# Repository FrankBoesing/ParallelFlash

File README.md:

# ParallelFlash

Compatibel to SerialFlash by Paul Stoffregen

Winbond SPI Flash only.

Connections:

Pin 1 (Flash) : Pin 5 (Teensy)

Pin 2 (Flash) : Pin 14(Teensy)

Pin 3 (Flash) : Pin 7(Teensy)

Pin 4 (Flash) : GND

Pin 5 (Flash) : Pin 2(Teensy)

Pin 6 (Flash) : Pin 20(Teensy)

Pin 7 (Flash) : Pin 8(Teensy)

Pin 8 (Flash) : 3.3Volt

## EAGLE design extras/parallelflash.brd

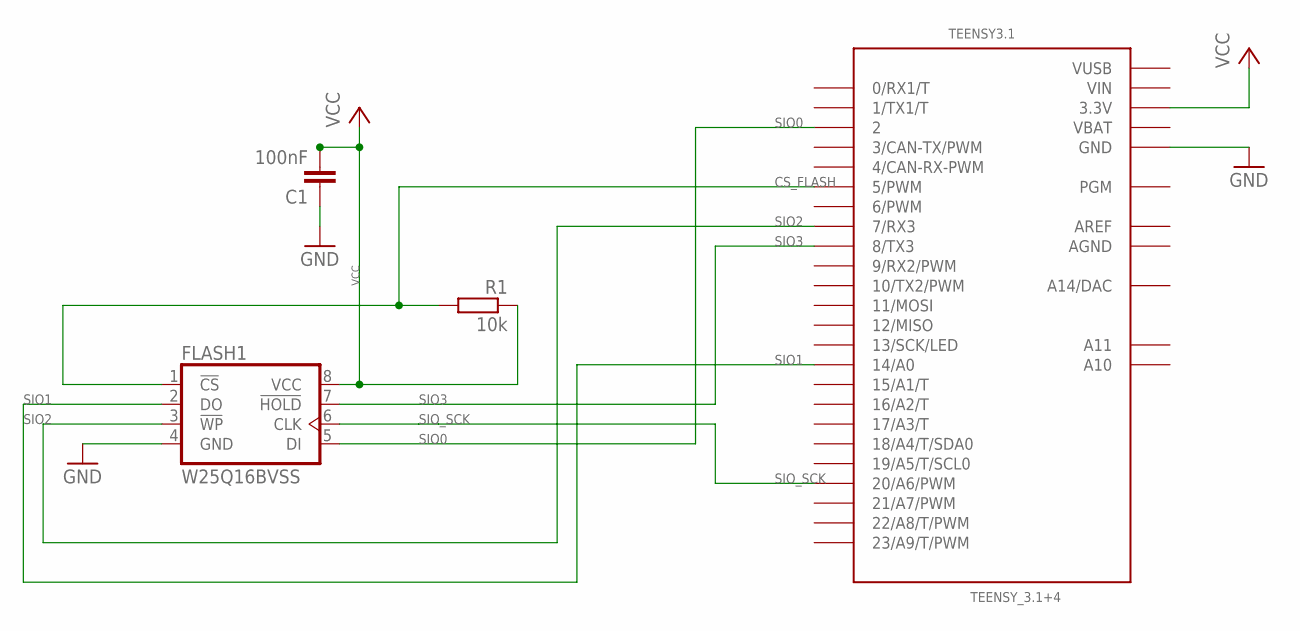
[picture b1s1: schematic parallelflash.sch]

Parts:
C1: 100nF; C0603
FLASH1: W25Q16BVSS; SO08-SS
R1: 10k; R0603
TEENSY3.1: TEENSY_3.1+4

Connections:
AGND: TEENSY3.1.AGND
AREF: TEENSY3.1.AREF
CS_FLASH: FLASH1.1 (!CS!), R1.2, TEENSY3.1.5 (5/PWM)
GND: C1.1, FLASH1.4 (GND), TEENSY3.1.GND, TEENSY3.1.GND1 (GND)
SIO0: FLASH1.5 (DI), TEENSY3.1.2
SIO1: FLASH1.2 (DO), TEENSY3.1.14/A0
SIO2: FLASH1.3 (!WP!), TEENSY3.1.7 (7/RX3)
SIO3: FLASH1.7 (!HOLD!), TEENSY3.1.8 (8/TX3)
SIO_SCK: FLASH1.6 (CLK), TEENSY3.1.20/A6 (20/A6/PWM)
VBAT: TEENSY3.1.VBAT
VCC: C1.2, FLASH1.8 (VCC), R1.1, TEENSY3.1.3.3V, TEENSY3.1.3.3V1 (3.3V)
VIN: TEENSY3.1.VIN
VUSB: TEENSY3.1.VUSB

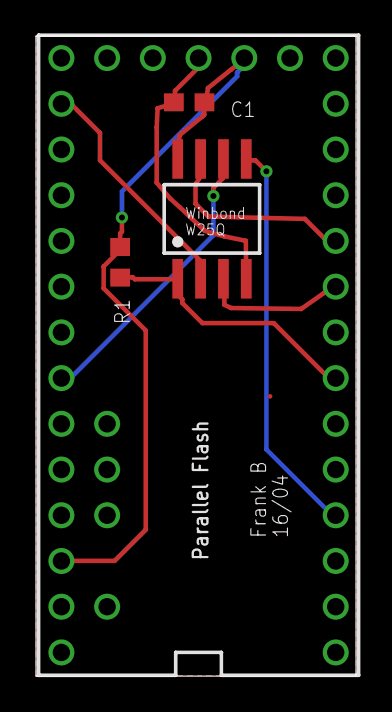
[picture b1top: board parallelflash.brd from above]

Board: 2 copper layers, 17.8 x 35.6 mm, 4 parts (0 on the bottom side), 8 nets.

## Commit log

2016-03-31 Initial commit
    2016/03/31, in sync with SerialFlash 0.4
2016-04-01 readSerialNumber(uint8_t *buf) //needs room for 8 bytes
2016-04-16 Add Speedtest example
2016-04-16 more speed
    read now 4.8 MegaBytes / sec @ 120MHz (3.9 before)
2016-04-16 a bit more speed with 32-Bit writes
    now 5.45 Megabyte / Sec
2016-04-17 Upload Eagle Board
2016-04-24 Some Updates
2016-04-28 return capacity=0 for missing connections
2016-04-29 rmv n

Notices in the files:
parts and their libraries:
winbond: Copyright (C) 2010, Bob Starr
